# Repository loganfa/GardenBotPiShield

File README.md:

# GardenBotPiShield
Open source pump control shield for raspberry pi 0

Still in progress... needs testing and code. Your mileage may vary!

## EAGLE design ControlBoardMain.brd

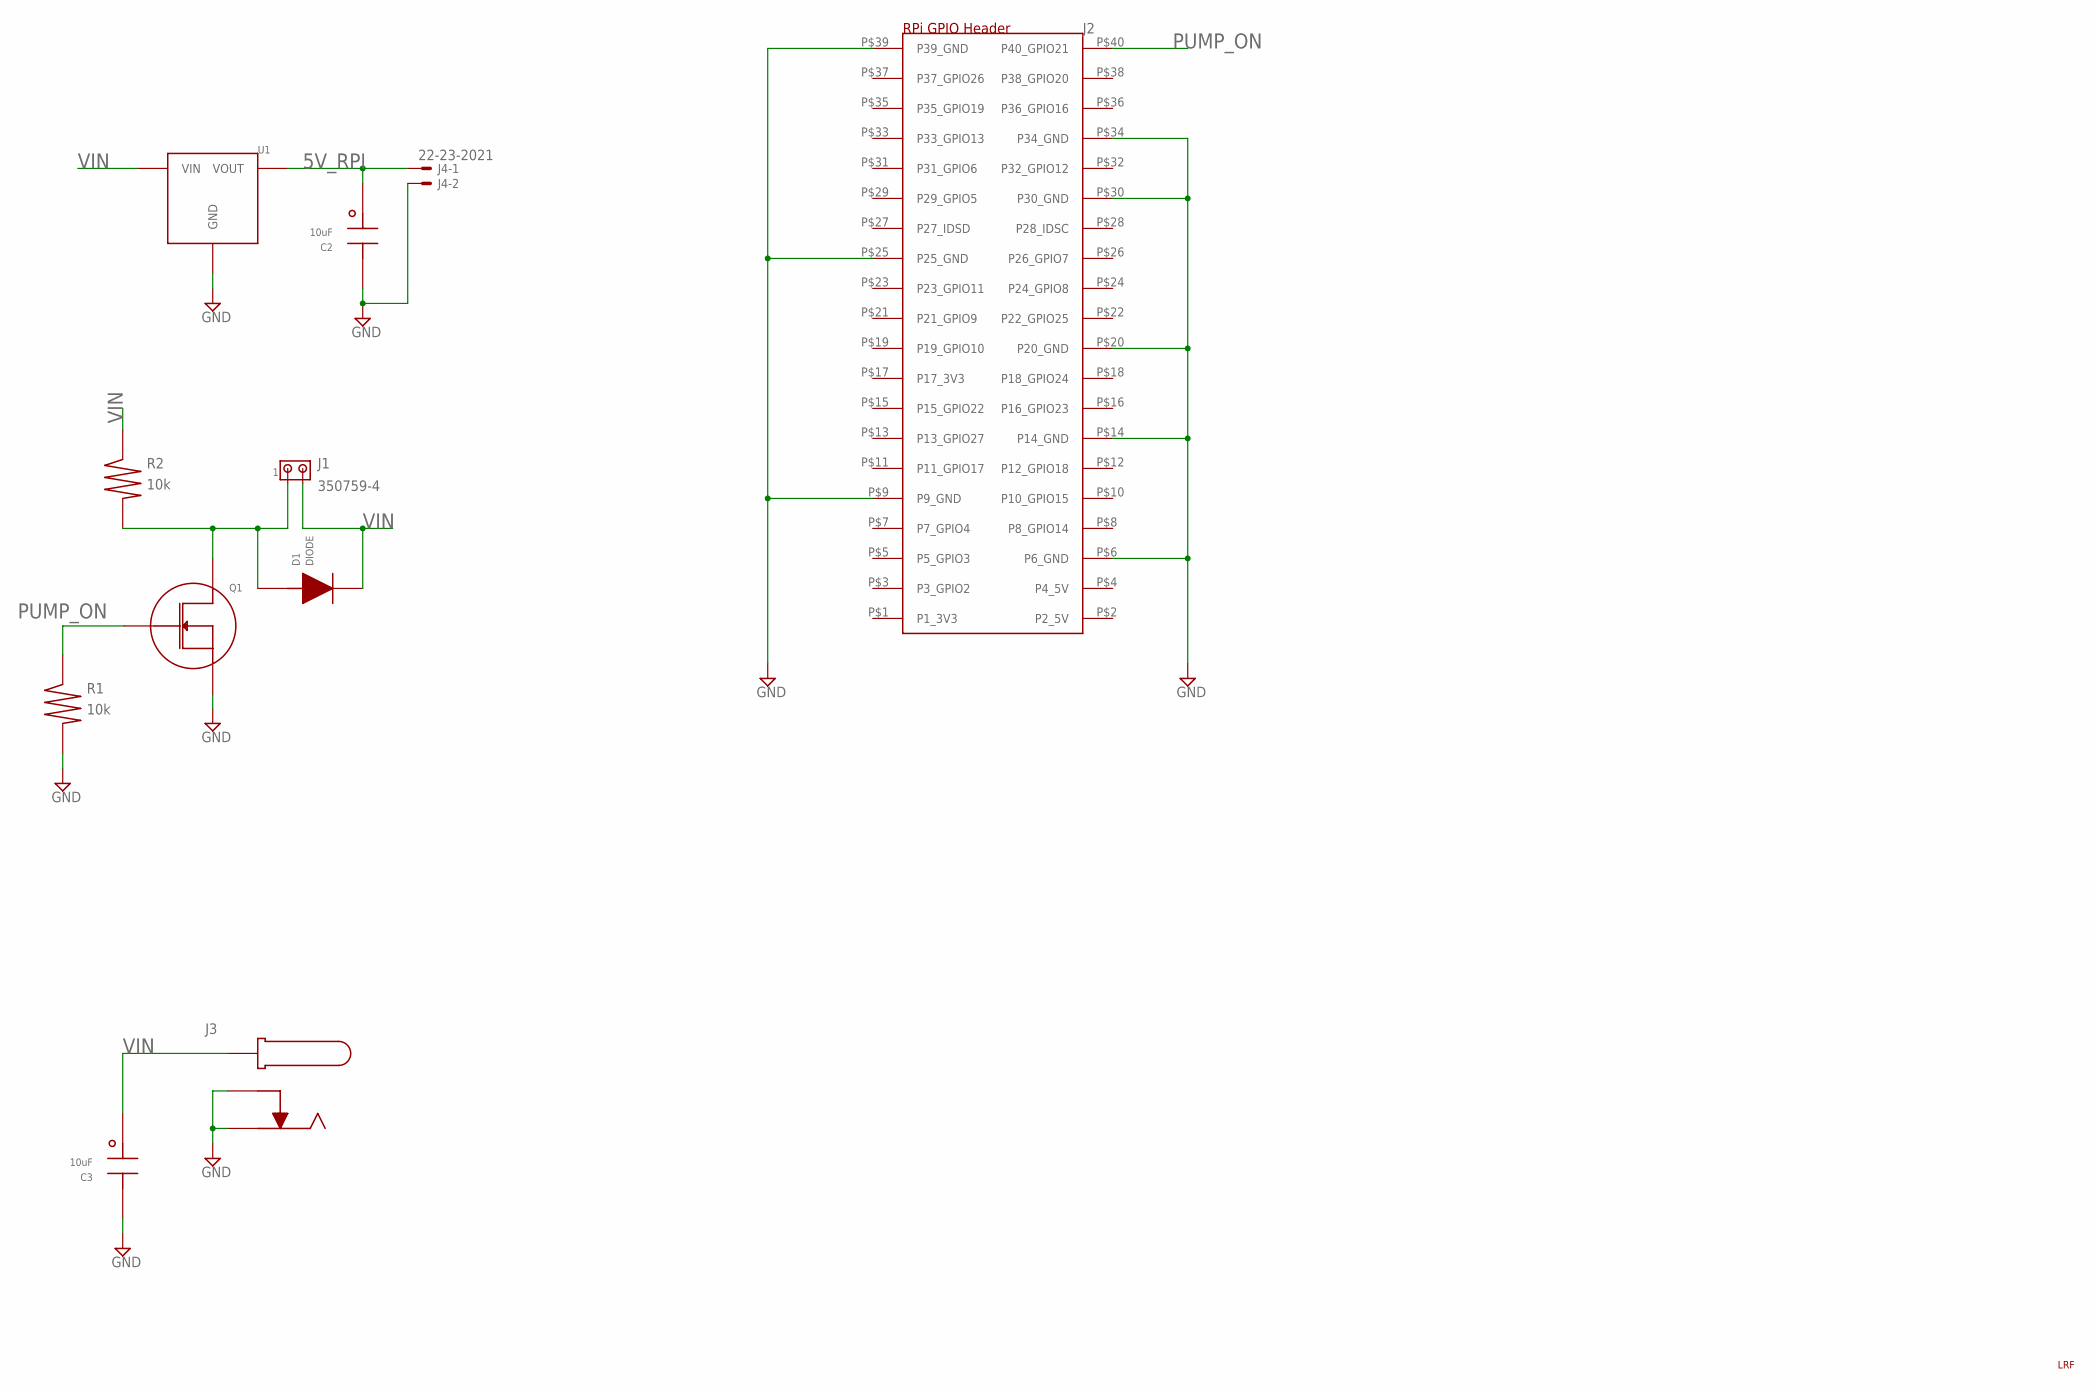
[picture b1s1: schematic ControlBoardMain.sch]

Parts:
C2, C3: 10uF; TH_PASSIVE
D1: DIODE; TH_PASSIVE
J1: 350759-4
J2: RPI_HEADER; RPIHEADER
J3: DC_POWERJACK
J4: 22-23-2021
Q1: NMOS; TH_3PIN
R1, R2: 10k; TH_PASSIVE
U1: VOLTAGE_REGULATOR; TH_3PIN
U$1: LOGO

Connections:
5V_RPI: C2.P1, J4.1, U1.P3 (VOUT)
GND: C2.P2, C3.P2, J2.P$6 (P6_GND), J2.P$9 (P9_GND), J2.P$14 (P14_GND), J2.P$20 (P20_GND), J2.P$25 (P25_GND), J2.P$30 (P30_GND), J2.P$34 (P34_GND), J2.P$39 (P39_GND), J3.P2, J3.P3, J4.2, Q1.P3 (SOURCE), R1.P2, U1.P2 (GND)
PUMP_GND: D1.P2, J1.1, Q1.P2 (DRAIN), R2.P2
PUMP_ON: J2.P$40 (P40_GPIO21), Q1.P1 (GATE), R1.P1
VIN: C3.P1, D1.P1, J1.2, J3.P1, R2.P1, U1.P1 (VIN)

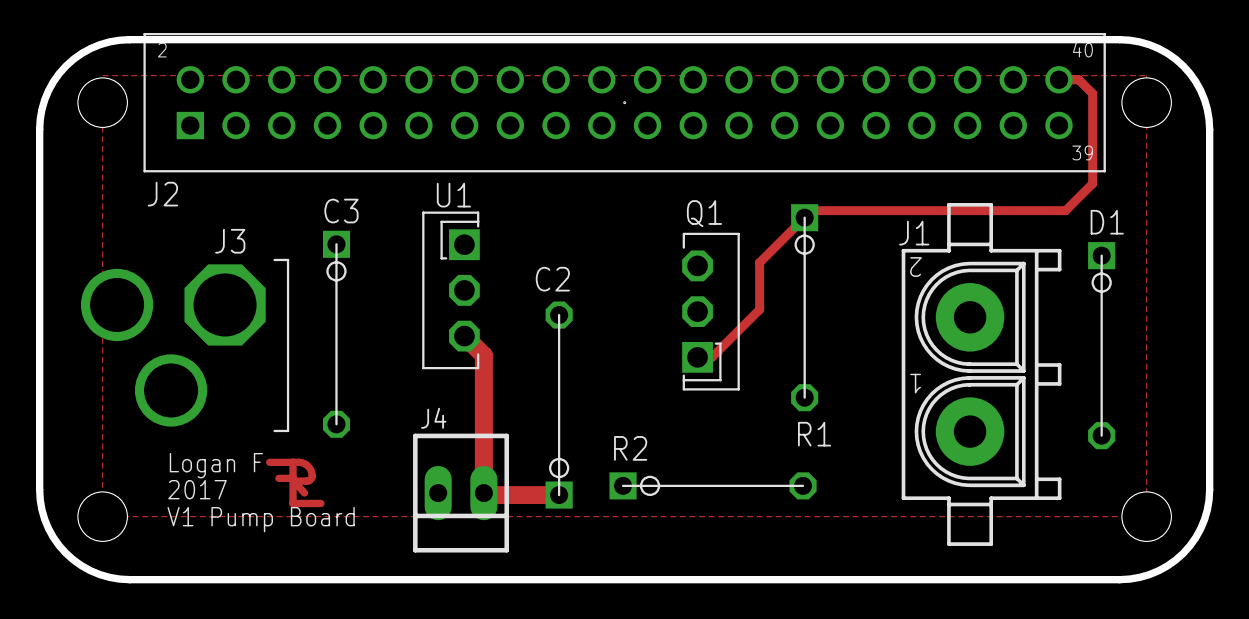
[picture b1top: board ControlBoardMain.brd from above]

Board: 2 copper layers, 65.0 x 30.0 mm, 12 parts (0 on the bottom side), 5 nets.

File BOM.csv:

Ref Des,Qty,Description,Part Number
U1,1,"5V Regulator, TO-220 Package",Generic
"R1, R2",2,10kOhm Through-Hole Resistor,Generic
"C2, C3",2,"10uFarad Capacitor, Pref. Ceramic",Generic
J1,1,"Pump Header, Vertical",TE-AMP 350759-4 or similar
J2,1,"2x20 0.1"" Pitch Header",Generic (Tall enough to interface boards)
J3,1,"DC Barrel Jack, CUI",CUI Inc PJ-202A
J4,1,Solder Connection. Do not populate.,N/A
D1,1,Flyback Diode,1N4004 or similar

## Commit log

2017-04-16 :neckbeard: Added .gitattributes & .gitignore files
2017-04-16 Added flyback diode
2017-04-16 Added readme
2017-04-16 Added dxf and pdf versions of schematic/layout
2017-04-16 Fixed the flyback diode
2017-04-16 Updated pdf/dxf for diode
2017-04-17 Updated .gitignore and various other docs
2017-04-17 deleted superfluous gerber zips
